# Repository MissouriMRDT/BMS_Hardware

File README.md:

Battery Management System- this year it DOES THINGS (for real though!).

New for 2022: <br/>
-Designed to monitor an 8s8p LiPo battery pack at a max 33.6V @ 160A peak. <br/>
-The Cell Monitoring circuit uses the AS358MTR-E1 Op-Amp as it could be powered off of pack voltage. <br/>
-Teensy 4.1 used as microcontroller for the board.

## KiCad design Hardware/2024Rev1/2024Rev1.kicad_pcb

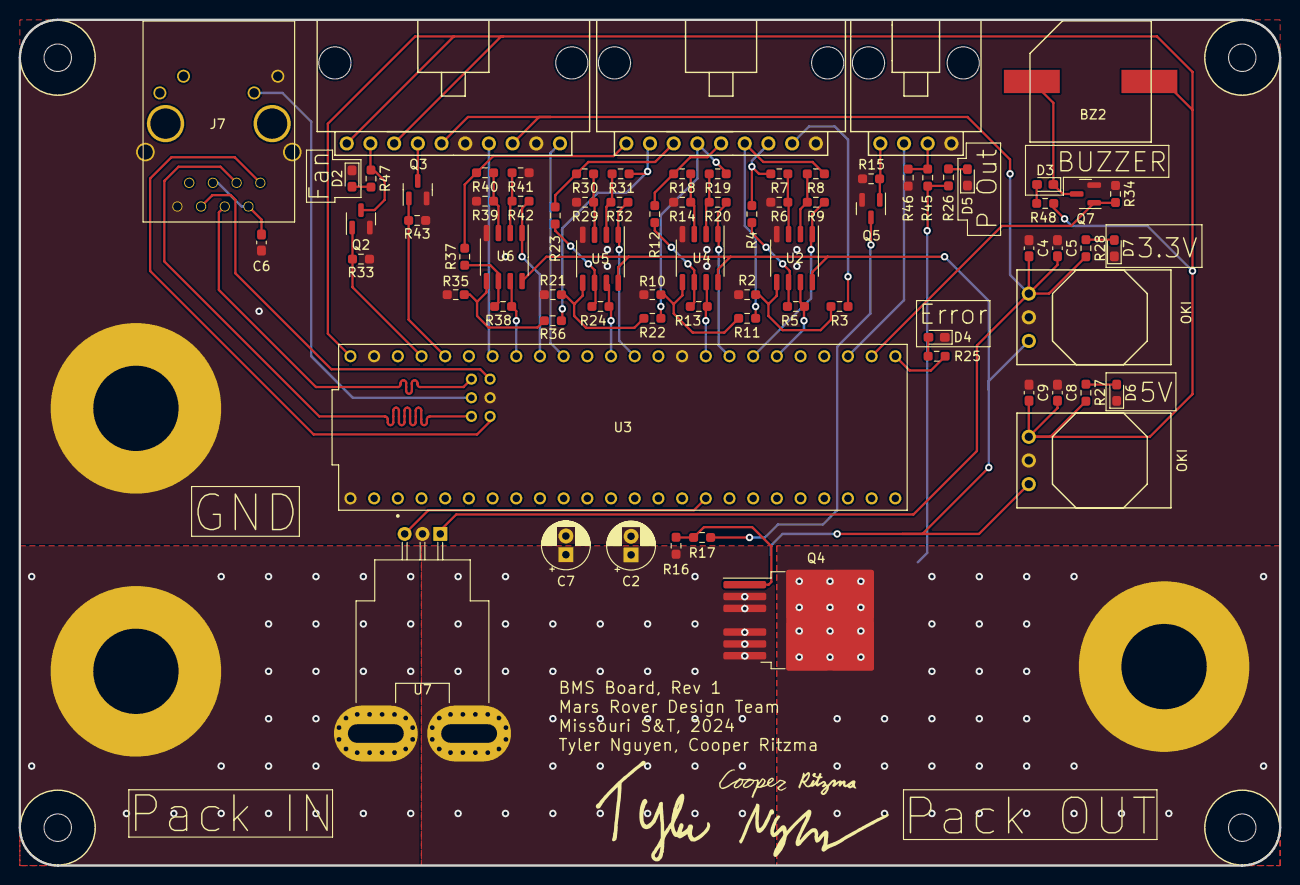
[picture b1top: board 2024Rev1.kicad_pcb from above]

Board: 2 copper layers, 135.1 x 90.7 mm, 84 parts (0 on the bottom side), 65 nets.

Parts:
BZ2: Buzzer; BUZZER_SMI_1324_TW_5V_2_R
C2, C7: 22uF; CP_Radial_D5.0mm_P2.00mm
C4, C8: 1uF; C_0603_1608Metric_Pad1.08x0.95mm_HandSolder
C5, C9: 10uF; C_0603_1608Metric_Pad1.08x0.95mm_HandSolder
C6: 0.1uF; C_0603_1608Metric_Pad1.08x0.95mm_HandSolder
Conn3: Molex_SL_09; MOLEX_SL_09_Horizontal
Conn4: Molex_SL_10; MOLEX_SL_10_Horizontal
Conn5: Molex_SL_04; MOLEX_SL_04_Horizontal
D2, D3, D5, D6, D7: Green; LED_0603_1608Metric_Pad1.05x0.95mm_HandSolder
D4: Red; LED_0603_1608Metric_Pad1.05x0.95mm_HandSolder
H1, H2, H3, H4: MountingHole; 4_40_Hole
J7: RJ45_LED_Shielded; RJ45_Teensy
Q2, Q3, Q5, Q7: BSS138; SOT-23
Q4: IPB180N10S4-02; TO-263-6
R2, R5, R6, R9, R10, R13, R14, R20, R21, R24, R29, R32, R35, R38, R39, R42: 36.5k; R_0603_1608Metric_Pad0.98x0.95mm_HandSolder
R3, R4, R7, R8, R11, R12, R18, R19, R22, R23, R30, R31, R36, R37, R40, R41: 46.4k; R_0603_1608Metric_Pad0.98x0.95mm_HandSolder
R15: 4.7K; R_0603_1608Metric_Pad0.98x0.95mm_HandSolder
R16, R17: 10K; R_0603_1608Metric_Pad0.98x0.95mm_HandSolder
R25, R28: 100; R_0603_1608Metric_Pad0.98x0.95mm_HandSolder
R26: 3k; R_0603_1608Metric_Pad0.98x0.95mm_HandSolder
R27, R47, R48: 300; R_0603_1608Metric_Pad0.98x0.95mm_HandSolder
R33, R34, R43: 4.7k; R_0603_1608Metric_Pad0.98x0.95mm_HandSolder
R45: 4k; R_0603_1608Metric_Pad0.98x0.95mm_HandSolder
R46: 10k; R_0603_1608Metric_Pad0.98x0.95mm_HandSolder
U2, U4, U5, U6: Opamp_Dual; SO-8_3.9x4.9mm_P1.27mm
U3: Teensy4.1_DEV-16771; Teensy_4_1_Ethernet
U7: ACS758xCB-200B-PFF; Allegro_CB_PFF
U8, U9: OKI; OKI_Horizontal
V2: BATT_GND_VIA; BATT_PWR_VIA
V3: BATT_PWR_VIA
V4: BMS_OUT_VIA; BATT_PWR_VIA

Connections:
+3.3V: C4.1, C5.1, Conn4.5, Conn4.8, R28.2, U7.1 (VCC), U9.3 (Vo)
+5V: BZ2.1 (-), C8.1, C9.1, Conn4.1, Conn4.3, R27.2, R48.2, U3.VIN, U8.3 (Vo)
Buzzer-Teensy: Q7.1 (G), R34.2, U3.34 (RX8)
CONTACTOR_INPUT: Q3.1 (G), R43.2, U3.22 (A8)
CONTACTOR_OUTPUT: Conn4.4, Q3.3 (D)
CURRENT_SENSE: U3.24 (A10), U7.3 (VIOUT)
Cell1-SENSE: R42.2, U3.18 (A4), U6.1
Cell2-SENSE: R38.2, U3.19 (A5), U6.7
Cell3-SENSE: R32.2, U3.14 (A0), U5.1
Cell4-SENSE: R24.2, U3.15 (A1), U5.7
Cell5-SENSE: R20.2, U3.40 (A16), U4.1
Cell6-SENSE: R13.2, U3.41 (A17), U4.7
Cell7-SENSE: R9.2, U2.1, U3.39 (A15)
Cell8-SENSE: R5.2, U2.7, U3.38 (A14)
ERR_LED: R25.2, U3.33 (MCLK2)
ESTOP: Conn5.2, U3.35 (TX8)
Fan: Conn4.2, Q2.3 (D), R47.2
Fan-Teensy: Q2.1 (G), R33.2, U3.23 (A9)
GND: C2.2, C4.2, C5.2, C6.2, C7.2, C8.2, C9.2, Conn3.9, Conn4.6, Conn4.9, Conn5.4, D2.1 (K), D4.1 (K), D5.1 (K), D6.1 (K), D7.1 (K), J7.8, J7.9, J7.SH, Q2.2 (S), Q3.2 (S), Q5.2 (S), Q7.2 (S), R2.1, R6.1, R10.1, R14.1, R15.2, R21.1, R29.1, R33.1, R34.1, R35.1, R39.1, R41.1, R43.1, R46.2, U2.4 (V-), U3.GND1 (GND), U3.GND2 (GND), U3.GND3 (GND), U3.GND5 (GND), U4.4 (V-), U5.4 (V-), U6.4 (V-), U7.2 (GND), U8.2 (GND), U9.2 (GND), V2.1
LCD_TX: Conn4.7, U3.20 (A6)
LED: J7.10, U3.LED
unnamed: BZ2.2 (+), D3.1 (K), Q7.3 (D)
unnamed: C6.1, J7.2, J7.5
unnamed: Conn5.3, R45.2, R46.1
unnamed: D2.2 (A), R47.1
unnamed: D3.2 (A), R48.1
unnamed: D4.2 (A), R25.1
unnamed: D5.2 (A), R26.1
unnamed: D6.2 (A), R27.1
unnamed: D7.2 (A), R28.1
unnamed: Q4.1 (G), R16.2, R17.1
unnamed: Q5.3 (D), R17.2
unnamed: Conn5.1, Q5.1 (G), R15.1
unnamed: R6.2, R7.2, U2.3 (+)
unnamed: R8.2, R9.1, U2.2 (-)
unnamed: R2.2, R3.2, U2.5 (+)
unnamed: R4.2, R5.1, U2.6 (-)
unnamed: R14.2, R18.2, U4.3 (+)
unnamed: R19.2, R20.1, U4.2 (-)
unnamed: R10.2, R11.2, U4.5 (+)
unnamed: R12.2, R13.1, U4.6 (-)
unnamed: R29.2, R30.2, U5.3 (+)
unnamed: R31.2, R32.1, U5.2 (-)
unnamed: R21.2, R22.2, U5.5 (+)
unnamed: R23.2, R24.1, U5.6 (-)
unnamed: R39.2, R40.2, U6.3 (+)
unnamed: R41.2, R42.1, U6.2 (-)
unnamed: R35.2, R36.2, U6.5 (+)
unnamed: R37.2, R38.1, U6.6 (-)
unnamed: U7.4 (IP+), V3.1
PACK_OUT: Q4.4 (D), R26.2, R45.1, V4.1
Pack: C2.1, C7.1, Q4.2 (S), Q4.3 (S), Q4.5 (S), Q4.6 (S), Q4.7 (S), R16.1, U2.8 (V+), U4.8 (V+), U5.8 (V+), U6.8 (V+), U7.5 (IP-), U8.1 (Vi), U9.1 (Vi)
R+: J7.4, U3.R+
R-: J7.6, U3.R-
T+: J7.1, U3.T+
T-: J7.3, U3.T-
TempSensor: Conn4.10, U3.17 (A3)
cell1: Conn3.1, R37.1, R40.1
cell2: Conn3.2, R31.1, R36.1
cell3: Conn3.3, R23.1, R30.1
cell4: Conn3.4, R19.1, R22.1
cell5: Conn3.5, R12.1, R18.1
cell6: Conn3.6, R8.1, R11.1
cell7: Conn3.7, R4.1, R7.1
cell8: Conn3.8, R3.1

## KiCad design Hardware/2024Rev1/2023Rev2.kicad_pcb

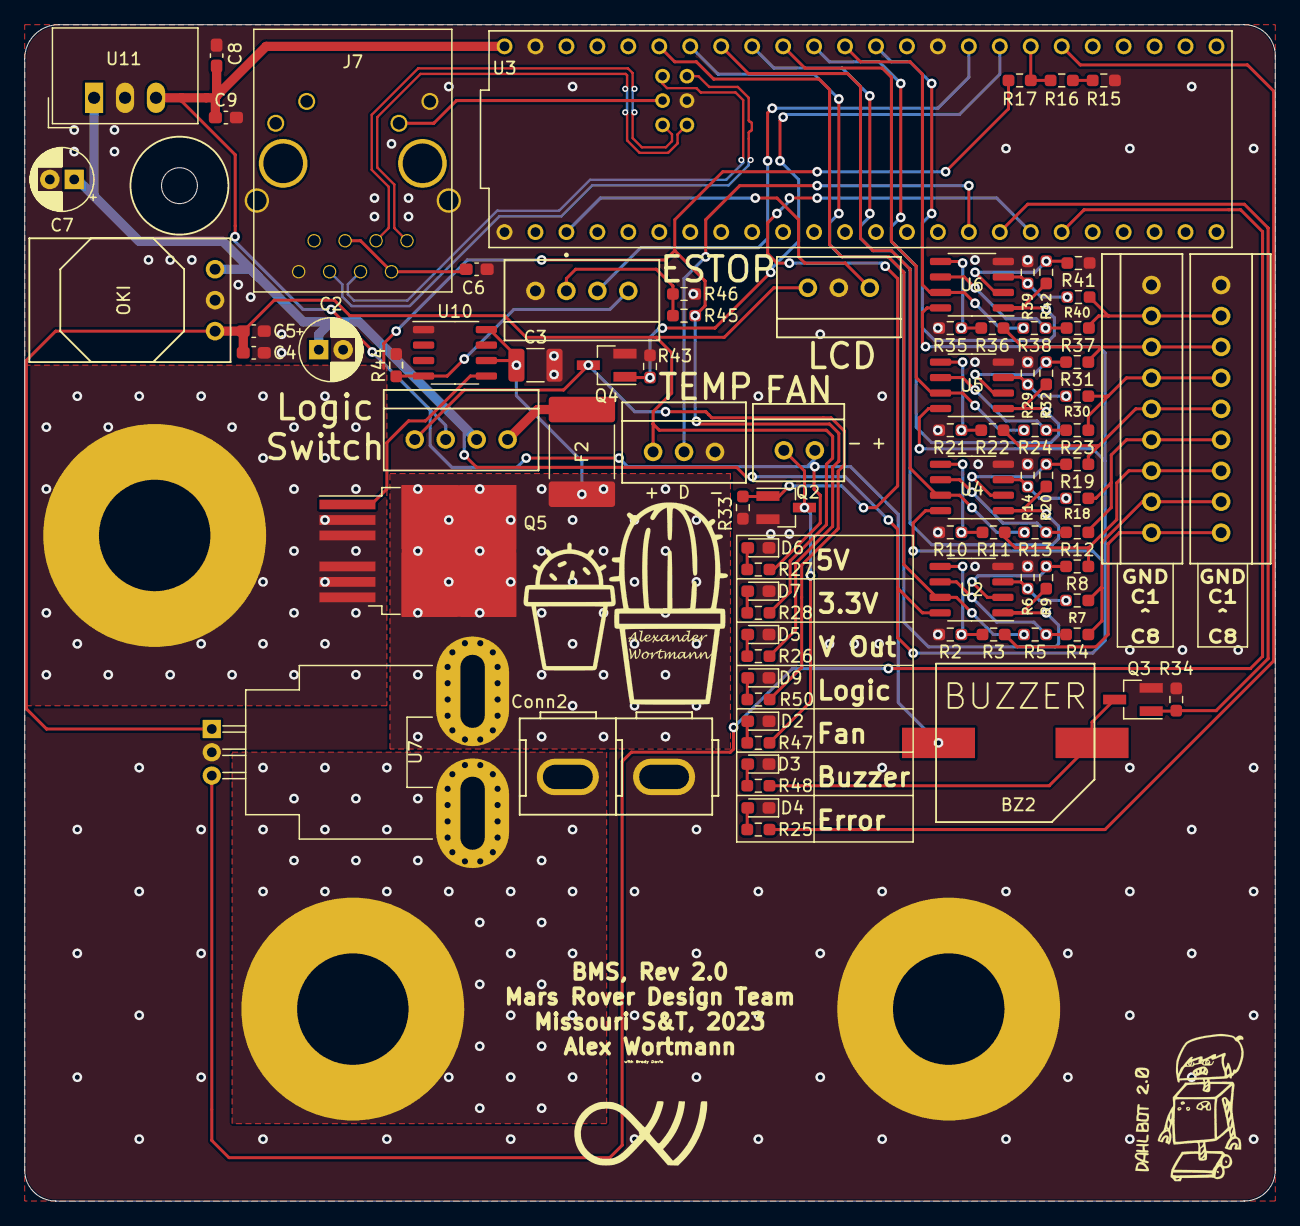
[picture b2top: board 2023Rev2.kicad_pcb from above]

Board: 2 copper layers, 102.6 x 96.5 mm, 91 parts (0 on the bottom side), 69 nets.

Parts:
BZ2: Buzzer; BUZZER_SMI_1324_TW_5V_2_R
C2, C7: 22uF; CP_Radial_D5.0mm_P2.00mm
C3: 10uF; C_1210_3225Metric_Pad1.33x2.70mm_HandSolder
C4, C8: 1uF; C_0603_1608Metric_Pad1.08x0.95mm_HandSolder
C5, C9: 10uF; C_0603_1608Metric_Pad1.08x0.95mm_HandSolder
C6: 0.1uF; C_0603_1608Metric_Pad1.08x0.95mm_HandSolder
Conn2: AndersonPP; Square_Anderson_2_V_Side_By_Side
D2, D3, D9: LED; LED_0603_1608Metric_Pad1.05x0.95mm_HandSolder
D4: ERR; LED_0603_1608Metric_Pad1.05x0.95mm_HandSolder
D5: PACK_OUT; LED_0603_1608Metric_Pad1.05x0.95mm_HandSolder
D6: 5V; LED_0603_1608Metric_Pad1.05x0.95mm_HandSolder
D7: 3V3; LED_0603_1608Metric_Pad1.05x0.95mm_HandSolder
F2: Polyfuse; Fuse_2920_7451Metric_Pad2.10x5.45mm_HandSolder
H3: MountingHole; 4_40_Hole
J2, J3: Conn_01x03; MOLEX_SL_03_Vertical
J4: Conn_01x02; MOLEX_SL_02_Vertical
J5, J6: Conn_01x09; MOLEX_SL_09_Vertical
J7: RJ45_LED_Shielded; RJ45_Teensy
J9: Conn_01x04; MOLEX_SL_04_Vertical
Q2, Q3, Q4: Q_NMOS_DGS; SOT-23_Handsoldering
Q5: Q_NMOS_GDS; IRLS3034_TO-263-7_P
R2, R5, R6, R9, R10, R13, R14, R20, R21, R24, R29, R32, R35, R38, R39, R42: 36.5k; R_0603_1608Metric_Pad0.98x0.95mm_HandSolder
R3, R4, R7, R8, R11, R12, R18, R19, R22, R23, R30, R31, R36, R37, R40, R41: 46.4k; R_0603_1608Metric_Pad0.98x0.95mm_HandSolder
R15: 820; R_0603_1608Metric_Pad0.98x0.95mm_HandSolder
R16, R44, R46: 10k; R_0603_1608Metric_Pad0.98x0.95mm_HandSolder
R17: 100K; R_0603_1608Metric_Pad0.98x0.95mm_HandSolder
R25, R28: 100; R_0603_1608Metric_Pad0.98x0.95mm_HandSolder
R26: 3k; R_0603_1608Metric_Pad0.98x0.95mm_HandSolder
R27: 300; R_0603_1608Metric_Pad0.98x0.95mm_HandSolder
R33, R34, R43: 4.7k; R_0603_1608Metric_Pad0.98x0.95mm_HandSolder
R45: 4k; R_0603_1608Metric_Pad0.98x0.95mm_HandSolder
R47, R48, R50: 75; R_0603_1608Metric_Pad0.98x0.95mm_HandSolder
U2, U4, U5, U6: Opamp_Dual; SO-8_3.9x4.9mm_P1.27mm
U3: Teensy4.1_DEV-16771; Teensy_4_1_Ethernet
U7: ACS758xCB-200B-PFF; Allegro_CB_PFF
U8: BMS_Logic_Switch; MOLEX_SL_04_Vertical
U9: OKI; OKI_Horizontal
U10: LT1910; SO-8_3.9x4.9mm_P1.27mm
U11: TSR_1-2450; Converter_DCDC_TRACO_TSR-1_THT
V2: BATT_GND_VIA; BATT_PWR_VIA
V3: BATT_PWR_VIA
V4: BMS_OUT_VIA; BATT_PWR_VIA

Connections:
+3.3V: C4.1, C5.1, J2.3, J3.1, R28.2, U7.1 (VCC), U9.3 (Vo)
+5V: BZ2.1 (-), C8.1, C9.1, J4.2, R27.2, U3.VIN, U8.2, U11.3 (Vout)
CURRENT_SENSE: U3.27 (A13), U7.3 (VIOUT)
Cell1-SENSE: R42.2, U3.14 (A0), U6.1
Cell2-SENSE: R38.2, U3.15 (A1), U6.7
Cell3-SENSE: R32.2, U3.16 (A2), U5.1
Cell4-SENSE: R24.2, U3.17 (A3), U5.7
Cell5-SENSE: R20.2, U3.18 (A4), U4.1
Cell6-SENSE: R13.2, U3.19 (A5), U4.7
Cell7-SENSE: R9.2, U2.1, U3.20 (A6)
Cell8-SENSE: R5.2, U2.7, U3.21 (A7)
ERR_LED: R25.2, U3.38 (A14)
GATE: J9.2, U3.41 (A17)
GND: C2.2, C3.2, C4.2, C5.2, C6.2, C7.2, C8.2, C9.2, Conn2.1 (GND), D2.1 (K), D3.1 (K), D4.1 (K), D5.1 (K), D6.1 (K), D7.1 (K), D9.1 (K), J2.2, J3.3, J5.9, J6.1, J7.8, J7.9, J7.SH, J9.4, Q2.2 (S), Q3.2 (S), Q4.2 (S), R2.2, R6.2, R10.2, R14.2, R15.2, R21.2, R29.2, R33.1, R34.1, R35.2, R39.2, R41.1, R43.1, R44.2, R46.2, U2.4 (V-), U3.GND1 (GND), U3.GND2 (GND), U3.GND3 (GND), U3.GND5 (GND), U4.4 (V-), U5.4 (V-), U6.4 (V-), U7.2 (GND), U9.2 (GND), U10.1 (GND), U11.2 (GND), V2.1
LCD_TX: J2.1, U3.1 (TX1)
LED: J7.10, U3.LED
LOGIC_SWITCH: Q4.1 (G), R43.2, U3.40 (A16)
unnamed: BZ2.2 (+), Q3.3 (D), R48.2
unnamed: C6.1, J7.2, J7.5
unnamed: Conn2.2 (V+Log), U7.4 (IP+), V3.1
unnamed: D4.2 (A), R25.1
unnamed: D5.2 (A), R26.1
unnamed: D6.2 (A), R27.1
unnamed: D7.2 (A), R28.1
unnamed: C3.1, F2.1, Q5.2 (D), U7.5 (IP-), U10.6 (SENSE), U10.8 (V+)
unnamed: F2.2, U8.4
unnamed: J3.2, U3.24 (A10)
unnamed: J4.1, Q2.3 (D), R47.2
unnamed: J9.1, R44.1, U10.4 (IN)
unnamed: J9.3, R45.2, R46.1
unnamed: Q2.1 (G), R33.2, U3.26 (A12)
unnamed: Q3.1 (G), R34.2, U3.25 (A11)
unnamed: Q4.3 (D), R50.1, U8.1
unnamed: Q5.1 (G), U10.5 (GATE)
unnamed: R2.1, R3.2, U2.5 (+)
unnamed: R4.2, R5.1, U2.6 (-)
unnamed: R6.1, R7.2, U2.3 (+)
unnamed: R8.2, R9.1, U2.2 (-)
unnamed: R10.1, R11.2, U4.5 (+)
unnamed: R12.2, R13.1, U4.6 (-)
unnamed: R14.1, R18.2, U4.3 (+)
unnamed: R15.1, R16.2
unnamed: R16.1, R17.1, U3.39 (A15)
unnamed: R19.2, R20.1, U4.2 (-)
unnamed: R21.1, R22.2, U5.5 (+)
unnamed: R23.2, R24.1, U5.6 (-)
unnamed: R29.1, R30.2, U5.3 (+)
unnamed: R31.2, R32.1, U5.2 (-)
unnamed: R35.1, R36.2, U6.5 (+)
unnamed: R37.2, R38.1, U6.6 (-)
unnamed: R39.1, R40.2, U6.3 (+)
unnamed: R41.2, R42.1, U6.2 (-)
unnamed: D2.2 (A), R47.1
unnamed: D3.2 (A), R48.1
unnamed: D9.2 (A), R50.2
PACK_OUT: Q5.3 (S), R17.2, R26.2, R45.1, V4.1
PackLogic: C2.1, C7.1, U2.8 (V+), U4.8 (V+), U5.8 (V+), U6.8 (V+), U8.3, U9.1 (Vi), U11.1 (Vin)
R+: J7.4, U3.R+
R-: J7.6, U3.R-
T+: J7.1, U3.T+
T-: J7.3, U3.T-
call6: J5.3, J6.7, R8.1, R11.1
cell1: J5.8, J6.2, R37.1, R40.1
cell2: J5.7, J6.3, R31.1, R36.1
cell3: J5.6, J6.4, R23.1, R30.1
cell4: J5.5, J6.5, R19.1, R22.1
cell5: J5.4, J6.6, R12.1, R18.1
cell7: J5.2, J6.8, R4.1, R7.1
cell8: J5.1, J6.9, R3.1

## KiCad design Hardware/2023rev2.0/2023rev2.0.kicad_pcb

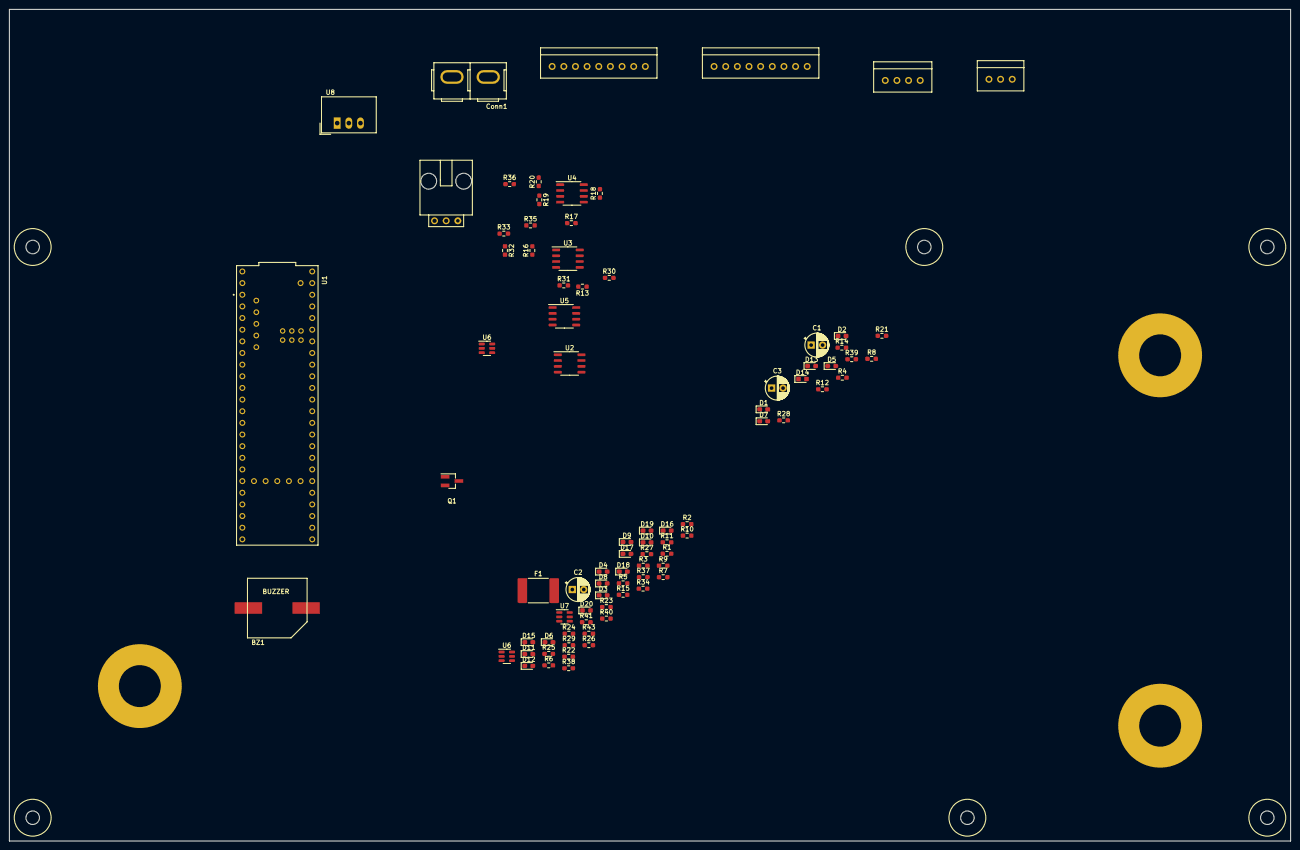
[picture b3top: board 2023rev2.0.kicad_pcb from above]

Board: 2 copper layers, 279.4 x 181.4 mm, 92 parts (0 on the bottom side), 57 nets, no tracks yet.

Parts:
BZ1: Buzzer; BUZZER_SMI_1324_TW_5V_2_R
C1: 22uF; CP_Radial_D5.0mm_P2.50mm
C2: 1uF; CP_Radial_D5.0mm_P2.50mm
C3: 10uF; CP_Radial_D5.0mm_P2.50mm
Conn1: AndersonPP; Square_Anderson_2_V_Side_By_Side_PV
D1: ERR; LED_0603_1608Metric_Pad1.05x0.95mm_HandSolder
D2: PACK_OUT; LED_0603_1608Metric_Pad1.05x0.95mm_HandSolder
D3: 5V; LED_0603_1608Metric_Pad1.05x0.95mm_HandSolder
D4: 3V3; LED_0603_1608Metric_Pad1.05x0.95mm_HandSolder
D5, D6, D7, D8, D9, D10, D11, D12: D_Schottky; D_0603_1608Metric_Pad1.05x0.95mm_HandSolder
D13, D14, D15, D16, D17, D18, D19, D20: D_Zener; D_0603_1608Metric_Pad1.05x0.95mm_HandSolder
F1: Polyfuse; Fuse_2920_7451Metric_Pad2.10x5.45mm_HandSolder
H1, H2, H3, H4, H5, H6: MountingHole; 4_40_Hole
J1: Conn_01x03; MOLEX_SL_03_Vertical
J2, J3: Conn_01x09; MOLEX_SL_09_Vertical
J4: Conn_01x04; MOLEX_SL_04_Vertical
Q1: Q_NMOS_DGS; SOT-23_Handsoldering
R1: 100K; R_0603_1608Metric_Pad0.98x0.95mm_HandSolder
R2: 4.7k; R_0603_1608Metric_Pad0.98x0.95mm_HandSolder
R3: 820; R_0603_1608Metric_Pad0.98x0.95mm_HandSolder
R4, R43: 10k; R_0603_1608Metric_Pad0.98x0.95mm_HandSolder
R5, R8: 100; R_0603_1608Metric_Pad0.98x0.95mm_HandSolder
R6: 3k; R_0603_1608Metric_Pad0.98x0.95mm_HandSolder
R7: 300; R_0603_1608Metric_Pad0.98x0.95mm_HandSolder
R9, R10, R11, R12, R13, R14, R15, R16, R17, R18, R19, R20, R21, R22, R23, R24: 31.5k; R_0603_1608Metric_Pad0.98x0.95mm_HandSolder
R25, R26, R27, R28, R29, R30, R31, R32, R33, R34, R35, R36, R37, R38, R39, R40: 40k; R_0603_1608Metric_Pad0.98x0.95mm_HandSolder
R41: 4k; R_0603_1608Metric_Pad0.98x0.95mm_HandSolder
SW1: SW_SPDT; MOLEX_SL_03_Horizontal
U1: Teensy4.1_DEV-16771; Teensy_4_1
U2, U3, U4, U5: Opamp_Dual; SO-8_3.9x4.9mm_P1.27mm
U6, U6#2, U7: INA195; SOT-23-6
U8: TSR_1-2450; Converter_DCDC_TRACO_TSR-1_THT
V1: BATT_GND_VIA; BATT_PWR_VIA
V2: BATT_PWR_VIA
V3: BMS_OUT_VIA; BATT_PWR_VIA

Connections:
+3.3V: C2.1, C3.1, J1.1, R8.2, U6.5 (V+), U6#2.5 (V+), U7.5 (V+)
+5V: BZ1.1 (-), R7.2, U2.8 (V+), U3.8 (V+), U4.8 (V+), U5.8 (V+), U8.3 (Vout)
GATE: J4.2, U1.41 (A17)
GND: C1.2, C2.2, C3.2, D1.1 (K), D2.1 (K), D3.1 (K), D4.1 (K), D12.2 (A), D13.2 (A), D14.2 (A), D15.2 (A), D16.2 (A), D17.2 (A), D18.2 (A), D19.2 (A), D20.2 (A), J1.3, J2.1, J3.1, J4.4, Q1.3 (S), R2.1, R3.2, R9.2, R11.2, R13.2, R15.2, R17.2, R19.2, R21.2, R23.2, R40.1, R43.1, U2.4 (V-), U3.4 (V-), U4.4 (V-), U5.4 (V-), U6.2 (GND), U6#2.2 (GND), U7.2 (GND), U8.2 (GND)
unnamed: BZ1.2 (+), Q1.1 (D)
unnamed: C1.1, SW1.2 (B), U8.1 (Vin)
unnamed: Conn1.1 (GND), V1.1
unnamed: D5.1 (K), D13.1 (K), J3.9, R25.1, V2.1
unnamed: D1.2 (A), R5.1
unnamed: D2.2 (A), R6.1
unnamed: D3.2 (A), R7.1
unnamed: D4.2 (A), R8.1
unnamed: D9.2 (A), D10.1 (K), D18.1 (K), J3.4, R34.1, R35.1
unnamed: D10.2 (A), D11.1 (K), D19.1 (K), J3.3, R36.1, R37.1
unnamed: D11.2 (A), D12.1 (K), D20.1 (K), J3.2, R38.1, R39.1
unnamed: D5.2 (A), D6.1 (K), D14.1 (K), J3.8, R26.1, R27.1
unnamed: D6.2 (A), D7.1 (K), D15.1 (K), J3.7, R28.1, R29.1
unnamed: D7.2 (A), D8.1 (K), D16.1 (K), J3.6, R30.1, R31.1
unnamed: D8.2 (A), D9.1 (K), D17.1 (K), J3.5, R32.1, R33.1
unnamed: F1.2, SW1.1 (A)
unnamed: J1.2, U1.21 (A7)
unnamed: J4.3, R41.1
unnamed: Q1.2 (G), R2.2, U1.20 (A6)
unnamed: R1.1, R4.1, U1.19 (A5)
unnamed: R3.1, R4.2
unnamed: R5.2, U1.22 (A8)
unnamed: R10.1, R26.2, U2.6 (-)
unnamed: R10.2, U1.40 (A16), U2.7
unnamed: R11.1, R27.2, U2.3 (+)
unnamed: R12.1, R28.2, U2.2 (-)
unnamed: R12.2, U1.39 (A15), U2.1
unnamed: R13.1, R29.2, U3.5 (+)
unnamed: R14.1, R30.2, U3.6 (-)
unnamed: R14.2, U1.38 (A14), U3.7
unnamed: R15.1, R31.2, U3.3 (+)
unnamed: R16.1, R32.2, U3.2 (-)
unnamed: R16.2, U1.27 (A13), U3.1
unnamed: R17.1, R33.2, U4.5 (+)
unnamed: R18.1, R34.2, U4.6 (-)
unnamed: R18.2, U1.26 (A12), U4.7
unnamed: R19.1, R35.2, U4.3 (+)
unnamed: R20.1, R36.2, U4.2 (-)
unnamed: R20.2, U1.25 (A11), U4.1
unnamed: R21.1, R37.2, U5.5 (+)
unnamed: R22.1, R38.2, U5.6 (-)
unnamed: R22.2, U1.24 (A10), U5.7
unnamed: R23.1, R39.2, U5.3 (+)
unnamed: R24.1, R40.2, U5.2 (-)
unnamed: R24.2, U1.23 (A9), U5.1
unnamed: R9.1, R25.2, U2.5 (+)
unnamed: U6#2.3 (+), U7.4 (-)
unnamed: U6#2.4 (-), U7.3 (+)
unnamed: U1.3.3V_1 (3.3V), U1.3.3V_2 (3.3V), U1.3.3V_3 (3.3V)
unnamed: U1.12 (MISO), U6.1, U6#2.1
unnamed: U1.GND1 (GND), U1.GND2 (GND), U1.GND3 (GND), U1.GND4 (GND), U1.GND5 (GND)
unnamed: U1.USB_GND1 (USB_GND), U1.USB_GND2 (USB_GND)
PACK_OUT: R1.2, R6.2, R41.2, R43.2, V3.1

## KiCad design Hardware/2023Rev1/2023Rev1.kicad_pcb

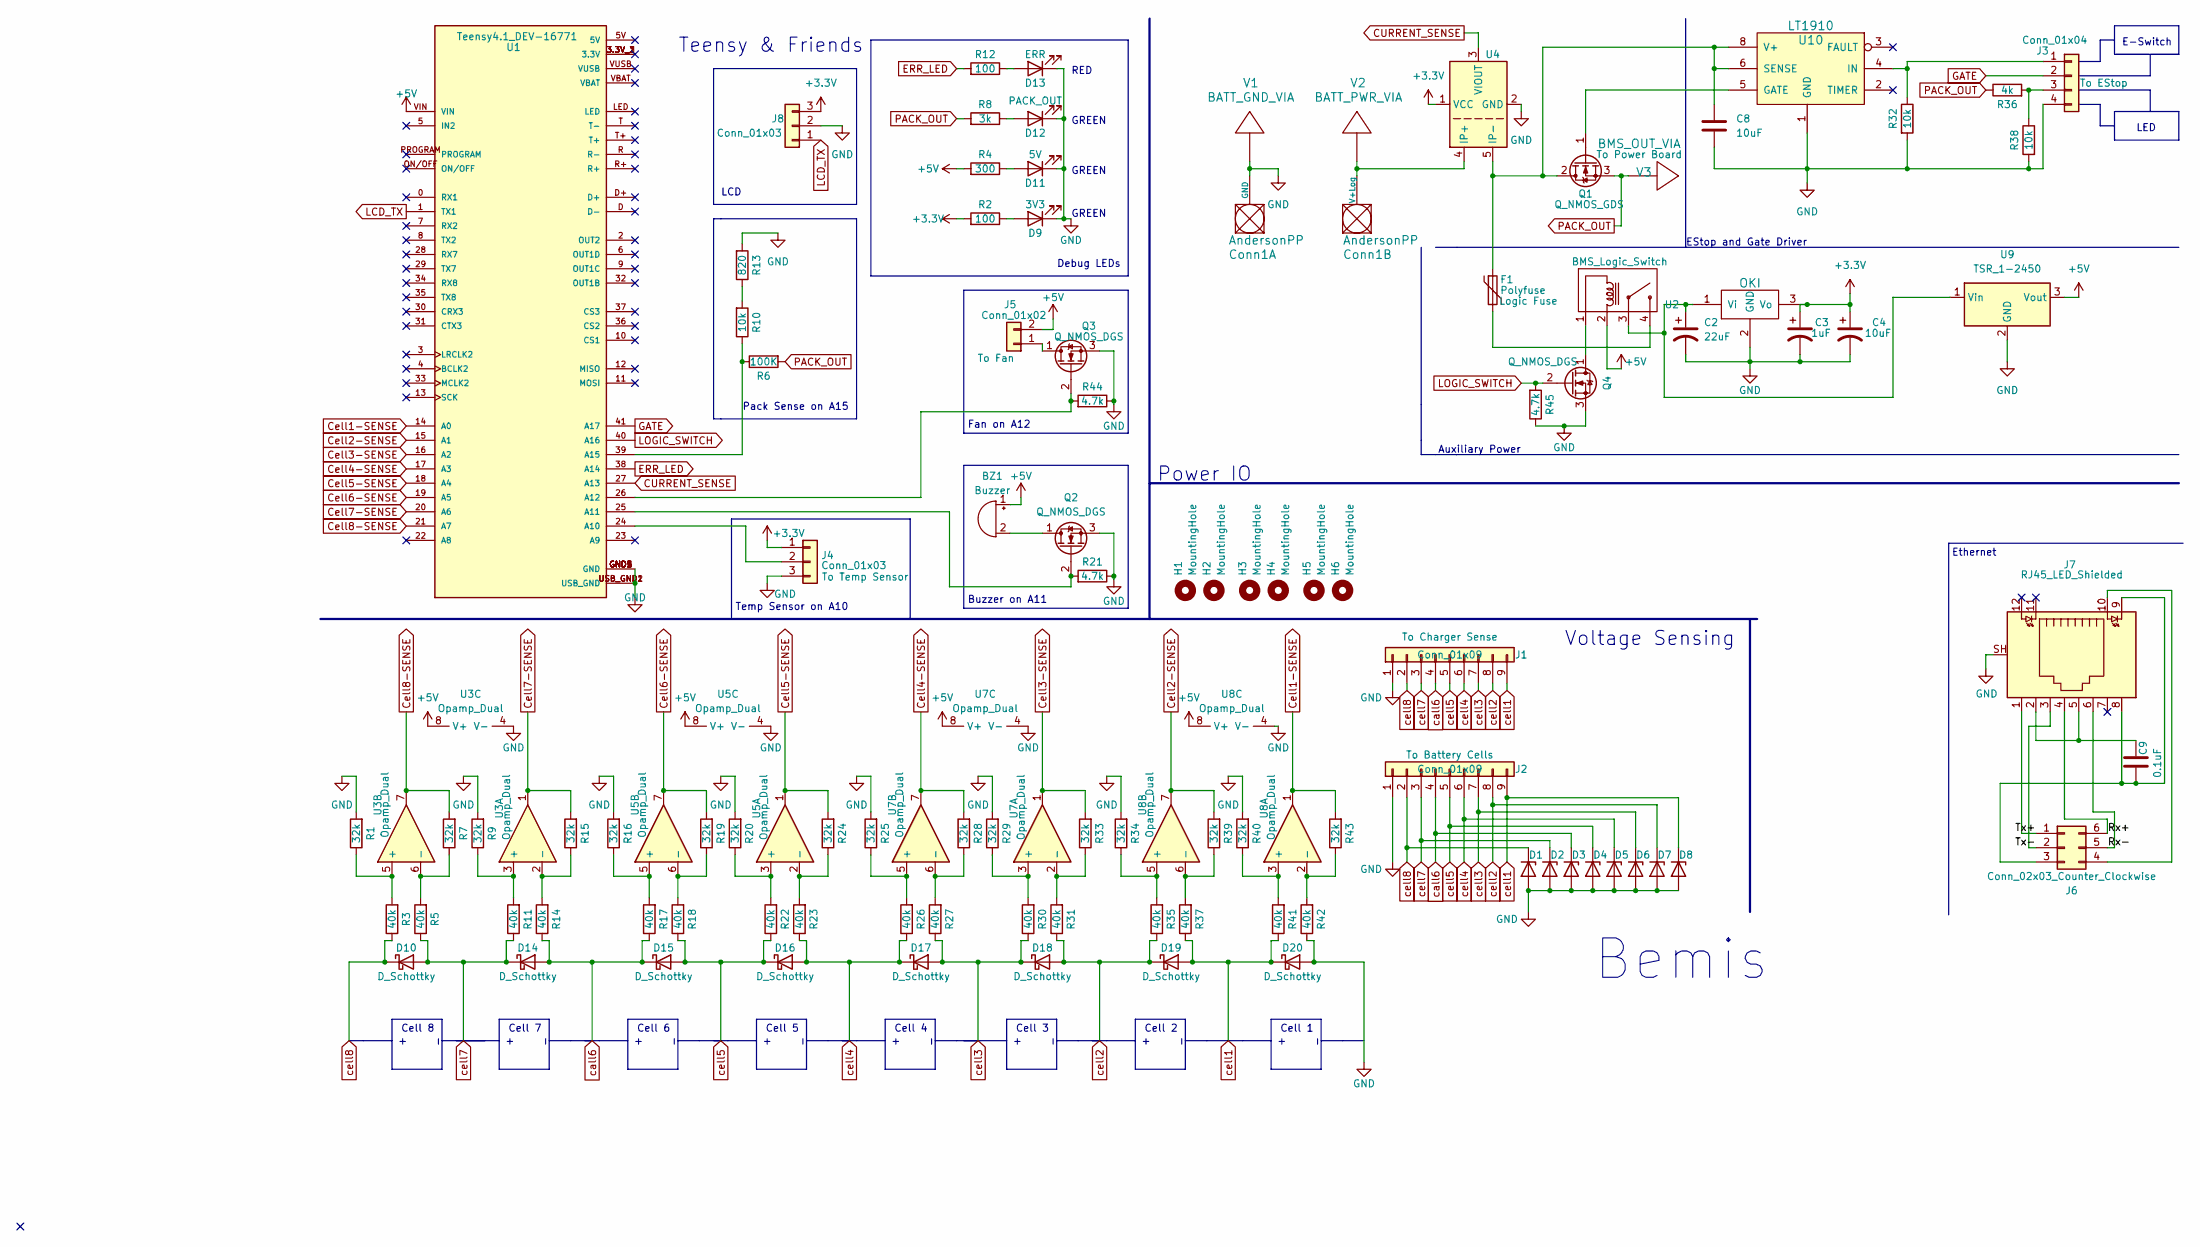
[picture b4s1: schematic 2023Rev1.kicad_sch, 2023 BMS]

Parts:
BZ1: Buzzer; BUZZER_SMI_1324_TW_5V_2_R
C2: 22uF; C_0603_1608Metric_Pad1.08x0.95mm_HandSolder
C3: 1uF; C_0603_1608Metric_Pad1.08x0.95mm_HandSolder
C4, C8: 10uF; C_0603_1608Metric_Pad1.08x0.95mm_HandSolder
C9: 0.1uF; C_0603_1608Metric_Pad1.08x0.95mm_HandSolder
Conn1: AndersonPP; Square_Anderson_2_V_Side_By_Side
D1, D2, D3, D4, D5, D6, D7, D8: D_Zener; SOT-23
D9: 3V3; LED_0603_1608Metric_Pad1.05x0.95mm_HandSolder
D10, D14, D15, D16, D17, D18, D19, D20: D_Schottky; D_SOD-123
D11: 5V; LED_0603_1608Metric_Pad1.05x0.95mm_HandSolder
D12: PACK_OUT; LED_0603_1608Metric_Pad1.05x0.95mm_HandSolder
D13: ERR; LED_0603_1608Metric_Pad1.05x0.95mm_HandSolder
F1: Polyfuse; Fuse_2920_7451Metric_Pad2.10x5.45mm_HandSolder
H1, H2, H3, H4: MountingHole; 4_40_Hole_Corner
H5, H6: MountingHole; 4_40_Hole
J1, J2: Conn_01x09; MOLEX_SL_09_Vertical
J3: Conn_01x04; MOLEX_SL_04_Vertical
J4, J8: Conn_01x03; MOLEX_SL_03_Vertical
J5: Conn_01x02; MOLEX_SL_02_Vertical
J6: Conn_02x03_Counter_Clockwise; PinHeader_2x03_P2.54mm_Vertical
J7: RJ45_LED_Shielded; RJ45_Teensy
Q1: Q_NMOS_GDS; IRLS3034_TO-263-7_P
Q2, Q3, Q4: Q_NMOS_DGS; SOT-23_Handsoldering
R1, R7, R9, R15, R16, R19, R20, R24, R25, R28, R29, R33, R34, R39, R40, R43: 32k; R_0603_1608Metric_Pad0.98x0.95mm_HandSolder
R2, R12: 100; R_0603_1608Metric_Pad0.98x0.95mm_HandSolder
R3, R5, R11, R14, R17, R18, R22, R23, R26, R27, R30, R31, R35, R37, R41, R42: 40k; R_0603_1608Metric_Pad0.98x0.95mm_HandSolder
R4: 300; R_0603_1608Metric_Pad0.98x0.95mm_HandSolder
R6: 100K; R_0603_1608Metric_Pad0.98x0.95mm_HandSolder
R8: 3k; R_0603_1608Metric_Pad0.98x0.95mm_HandSolder
R10, R32, R38: 10k; R_0603_1608Metric_Pad0.98x0.95mm_HandSolder
R13: 820; R_0603_1608Metric_Pad0.98x0.95mm_HandSolder
R21, R44, R45: 4.7k; R_0603_1608Metric_Pad0.98x0.95mm_HandSolder
R36: 4k; R_0603_1608Metric_Pad0.98x0.95mm_HandSolder
U1: Teensy4.1_DEV-16771; Teensy_4_1; PARTREV 4.1
U2: BMS_Logic_Switch; MOLEX_SL_04_Vertical
U3, U5, U7, U8: Opamp_Dual; SO-8_3.9x4.9mm_P1.27mm
U4: ACS758xCB-200B-PFF; Allegro_CB_PFF
U6: OKI; OKI_Horizontal
U9: TSR_1-2450; Converter_DCDC_TRACO_TSR-1_THT
U10: LT1910; SO-8_3.9x4.9mm_P1.27mm
V1: BATT_GND_VIA; BATT_PWR_VIA
V2: BATT_PWR_VIA
V3: BMS_OUT_VIA; BATT_PWR_VIA

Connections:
+3.3V: C3.1, C4.1, J4.1, J8.3, R2.2, U4.1 (VCC), U6.3 (Vo)
+5V: BZ1.1 (-), J5.2, R4.2, U1.VIN, U2.2, U3.8 (V+), U5.8 (V+), U7.8 (V+), U8.8 (V+), U9.3 (Vout)
/Rx+: J6.6, J7.4
/Rx-: J6.5, J7.6
/Tx+: J6.1, J7.1
/Tx-: J6.2, J7.3
CURRENT_SENSE: U1.27 (A13), U4.3 (VIOUT)
Cell1-SENSE: R43.2, U1.14 (A0), U8.1
Cell2-SENSE: R39.2, U1.15 (A1), U8.7
Cell3-SENSE: R33.2, U1.16 (A2), U7.1
Cell4-SENSE: R28.2, U1.17 (A3), U7.7
Cell5-SENSE: R24.2, U1.18 (A4), U5.1
Cell6-SENSE: R19.2, U1.19 (A5), U5.7
Cell7-SENSE: R15.2, U1.20 (A6), U3.1
Cell8-SENSE: R7.2, U1.21 (A7), U3.7
ERR_LED: R12.2, U1.38 (A14)
GATE: J3.2, U1.41 (A17)
GND: C2.2, C3.2, C4.2, C8.2, Conn1.1 (GND), D1.2 (A), D2.2 (A), D3.2 (A), D4.2 (A), D5.2 (A), D6.2 (A), D7.2 (A), D8.2 (A), D9.1 (K), D11.1 (K), D12.1 (K), D13.1 (K), D20.2 (A), J1.1, J2.1, J3.4, J4.3, J7.SH, J8.2, Q2.3 (S), Q3.3 (S), Q4.3 (S), R1.2, R9.2, R13.2, R16.2, R20.2, R21.1, R25.2, R29.2, R32.2, R34.2, R38.2, R40.2, R42.1, R44.1, R45.1, U1.GND1 (GND), U1.GND2 (GND), U1.GND3 (GND), U1.GND4 (GND), U1.GND5 (GND), U1.USB_GND1 (USB_GND), U1.USB_GND2 (USB_GND), U3.4 (V-), U4.2 (GND), U5.4 (V-), U6.2 (GND), U7.4 (V-), U8.4 (V-), U9.2 (GND), U10.1 (GND), V1.1
LCD_TX: J8.1, U1.1 (TX1)
LOGIC_SWITCH: Q4.2 (G), R45.2, U1.40 (A16)
unnamed: BZ1.2 (+), Q2.1 (D)
unnamed: C2.1, U2.3, U6.1 (Vi), U9.1 (Vin)
unnamed: C8.1, F1.1, Q1.2 (D), U4.5 (IP-), U10.6 (SENSE), U10.8 (V+)
unnamed: C9.1, J6.3, J7.8, J7.9
unnamed: C9.2, J7.2, J7.5
unnamed: Conn1.2 (V+Log), U4.4 (IP+), V2.1
unnamed: D9.2 (A), R2.1
unnamed: D11.2 (A), R4.1
unnamed: D12.2 (A), R8.1
unnamed: D13.2 (A), R12.1
unnamed: F1.2, U2.4
unnamed: J3.1, R32.1, U10.4 (IN)
unnamed: J3.3, R36.2, R38.1
unnamed: J4.2, U1.24 (A10)
unnamed: J5.1, Q3.1 (D)
unnamed: J6.4, J7.10
unnamed: Q1.1 (G), U10.5 (GATE)
unnamed: Q2.2 (G), R21.2, U1.25 (A11)
unnamed: Q3.2 (G), R44.2, U1.26 (A12)
unnamed: Q4.1 (D), U2.1
unnamed: R1.1, R3.2, U3.5 (+)
unnamed: R5.2, R7.1, U3.6 (-)
unnamed: R6.1, R10.1, U1.39 (A15)
unnamed: R10.2, R13.1
unnamed: R9.1, R11.2, U3.3 (+)
unnamed: R14.2, R15.1, U3.2 (-)
unnamed: R16.1, R17.2, U5.5 (+)
unnamed: R18.2, R19.1, U5.6 (-)
unnamed: R20.1, R22.2, U5.3 (+)
unnamed: R23.2, R24.1, U5.2 (-)
unnamed: R25.1, R26.2, U7.5 (+)
unnamed: R27.2, R28.1, U7.6 (-)
unnamed: R29.1, R30.2, U7.3 (+)
unnamed: R31.2, R33.1, U7.2 (-)
unnamed: R34.1, R35.2, U8.5 (+)
unnamed: R37.2, R39.1, U8.6 (-)
unnamed: R40.1, R41.2, U8.3 (+)
unnamed: R42.2, R43.1, U8.2 (-)
PACK_OUT: Q1.3 (S), R6.2, R8.2, R36.1, V3.1
call6: D3.1 (K), D14.2 (A), D15.1 (K), J1.4, J2.4, R14.1, R17.1
cell1: D8.1 (K), D19.2 (A), D20.1 (K), J1.9, J2.9, R37.1, R41.1
cell2: D7.1 (K), D18.2 (A), D19.1 (K), J1.8, J2.8, R31.1, R35.1
cell3: D6.1 (K), D17.2 (A), D18.1 (K), J1.7, J2.7, R27.1, R30.1
cell4: D5.1 (K), D16.2 (A), D17.1 (K), J1.6, J2.6, R23.1, R26.1
cell5: D4.1 (K), D15.2 (A), D16.1 (K), J1.5, J2.5, R18.1, R22.1
cell7: D2.1 (K), D10.2 (A), D14.1 (K), J1.3, J2.3, R5.1, R11.1
cell8: D1.1 (K), D10.1 (K), J1.2, J2.2, R3.1

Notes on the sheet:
Debug LEDs
Auxiliary Power
Power IO
Pack Sense on A15
Cell 1
GREEN
Bemis
Temp Sensor on A10
EStop and Gate Driver
Cell 2
Cell 7
Cell 8
Buzzer on A11
Cell 3
Cell 5
RED
LED
Fan on A12
Cell 6
LCD
Ethernet
E-Switch
Voltage Sensing
Teensy & Friends
Cell 4

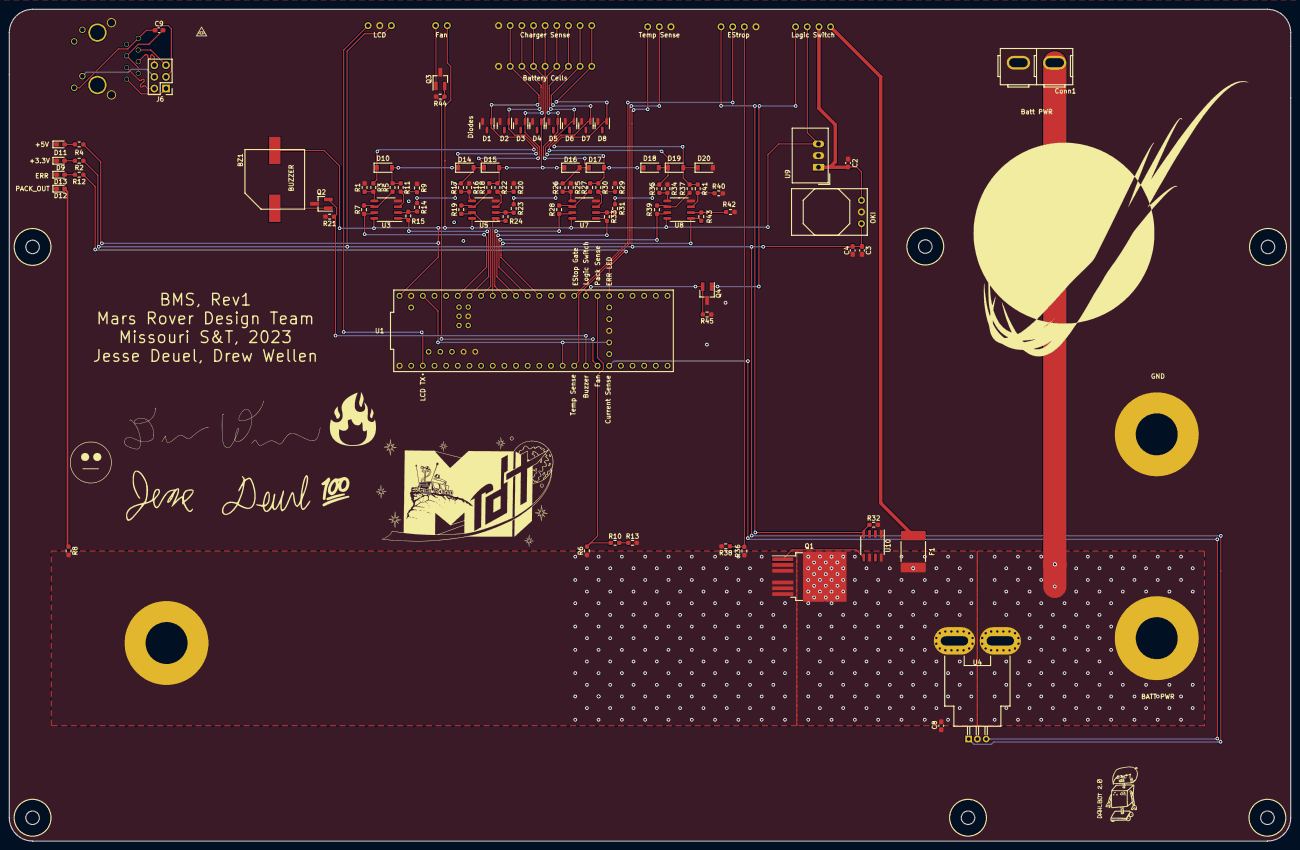
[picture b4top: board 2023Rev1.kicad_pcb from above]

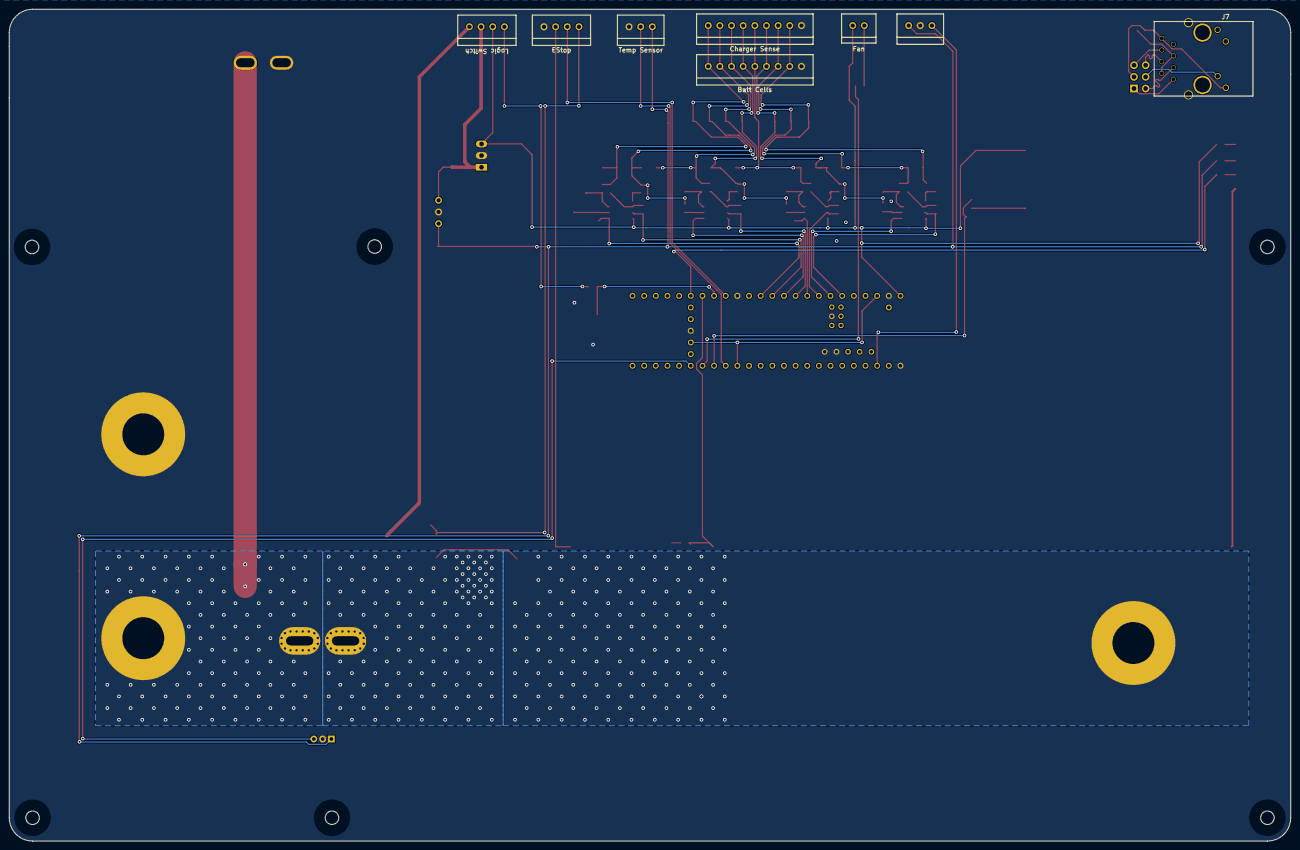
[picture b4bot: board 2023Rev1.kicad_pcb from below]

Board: 2 copper layers, 279.4 x 181.4 mm, 104 parts (8 on the bottom side), 67 nets.

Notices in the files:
parts and their libraries:
Copyright 2021 Accelerated Designs. All rights reserved.
